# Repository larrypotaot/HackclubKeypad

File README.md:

# 60% Keyboard Addon
* A roughly 3x6 layout for F row and arrow keys, alongside an audio knob. It is hot-swappable for cherry-mx switches.
* Uses QMK software

# PCB

Schematic

Layout: https://www.keyboard-layout-editor.com/#/gists/ed5083c6de0b27ba4e196096e7faea45

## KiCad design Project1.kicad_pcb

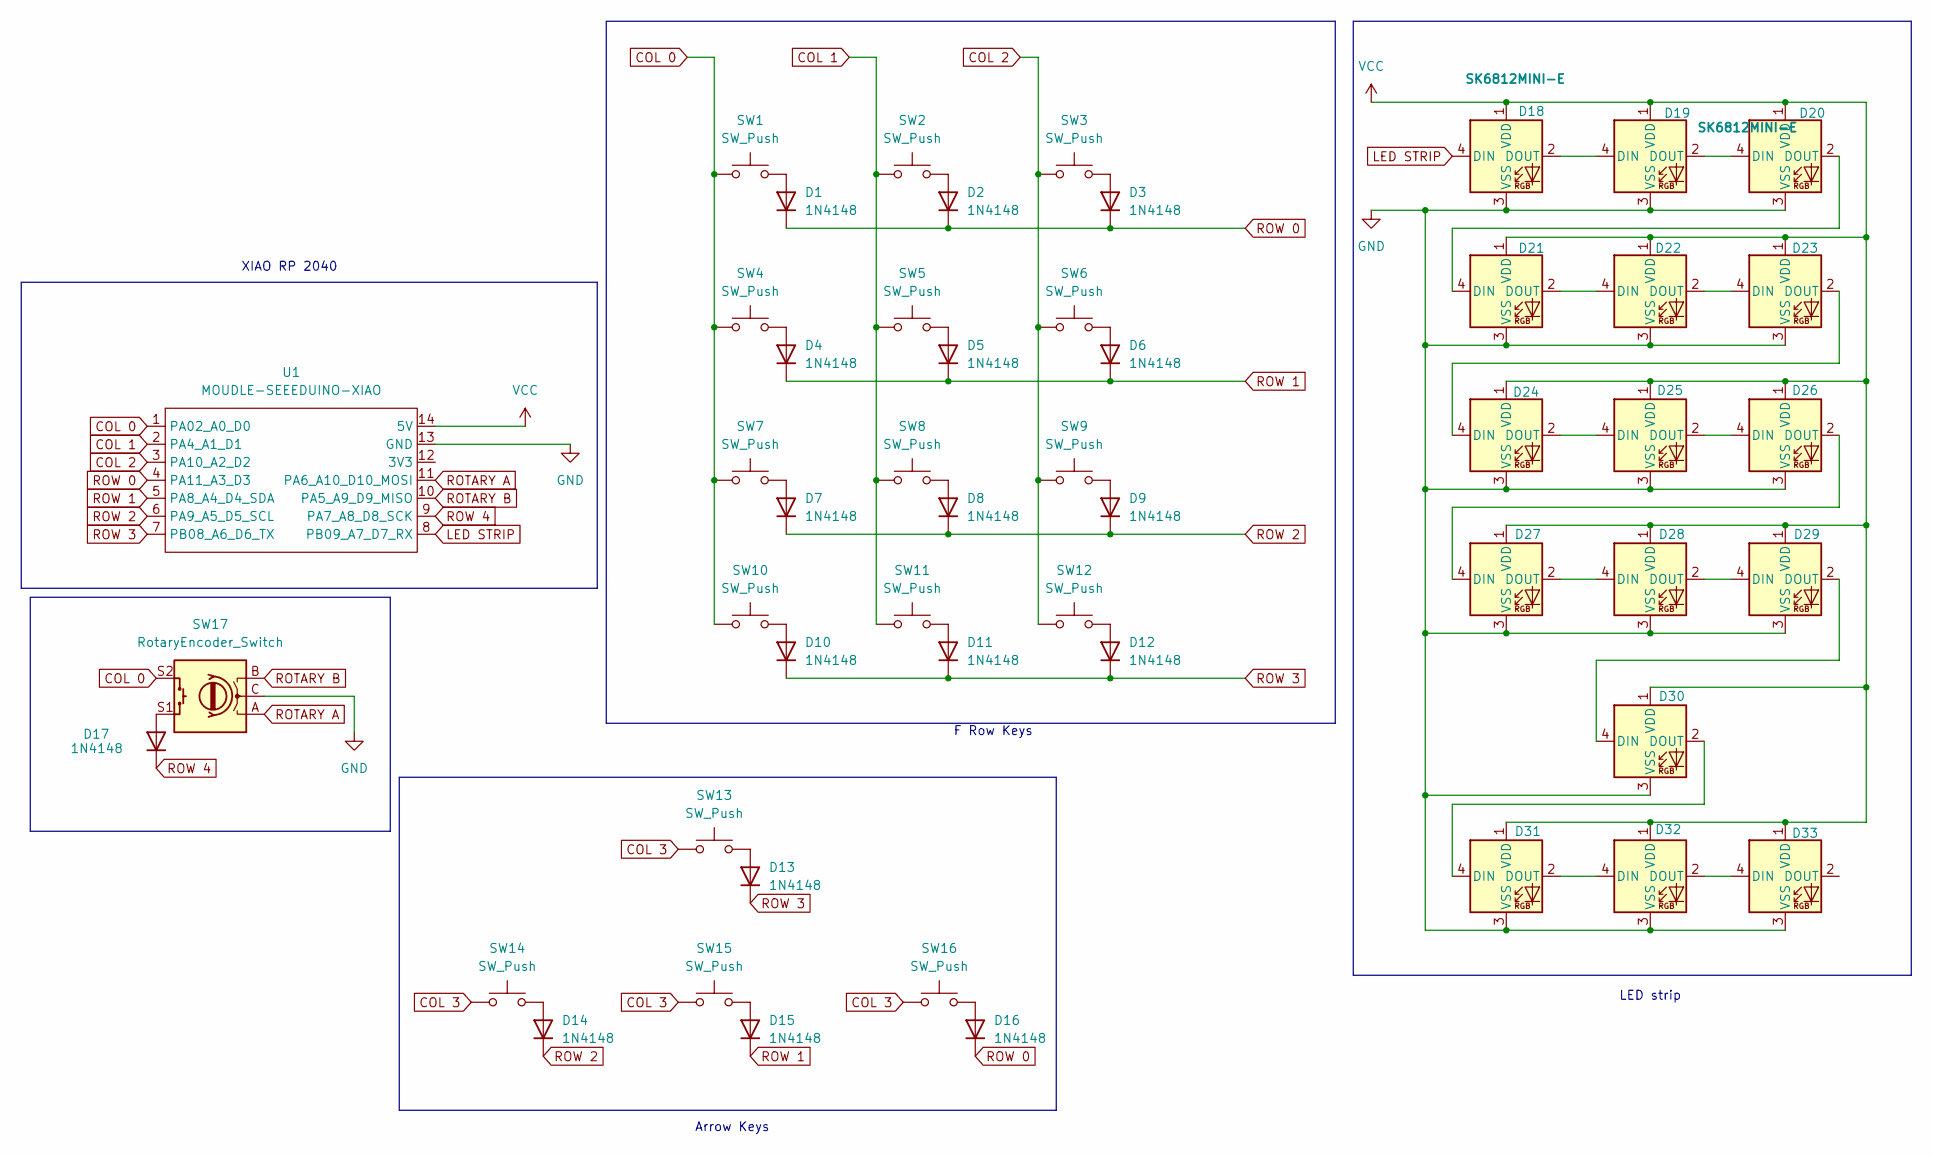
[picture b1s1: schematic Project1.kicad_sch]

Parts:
D1, D2, D3, D4, D5, D6, D7, D8, D9, D10, D11, D12, D13, D14, D15, D16, D17: 1N4148; D_DO-35_SOD27_P7.62mm_Horizontal
D18, D19, D20, D21, D22, D23, D24, D25, D26, D27, D28, D29, D30, D31, D32, D33: SK6812MINI-E; SK6812MINI-E_fixed
SW1, SW2, SW3, SW4, SW5, SW6, SW7, SW8, SW9, SW10, SW11, SW12, SW13, SW14, SW15, SW16: SW_Push; Hotswap_MX_1.00u
SW17: RotaryEncoder_Switch; RotaryEncoder_Alps_EC11E-Switch_Vertical_H20mm
U1: MOUDLE-SEEEDUINO-XIAO; XIAO-Generic-Hybrid-14P-2.54-21X17.8MM

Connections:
COL 0: SW1.1, SW4.1, SW7.1, SW10.1, SW17.S2, U1.1 (PA02_A0_D0)
COL 1: SW2.1, SW5.1, SW8.1, SW11.1, U1.2 (PA4_A1_D1)
COL 2: SW3.1, SW6.1, SW9.1, SW12.1, U1.3 (PA10_A2_D2)
COL 3: SW13.1, SW14.1, SW15.1, SW16.1
GND: D18.3 (VSS), D19.3 (VSS), D20.3 (VSS), D21.3 (VSS), D22.3 (VSS), D23.3 (VSS), D24.3 (VSS), D25.3 (VSS), D26.3 (VSS), D27.3 (VSS), D28.3 (VSS), D29.3 (VSS), D30.3 (VSS), D31.3 (VSS), D32.3 (VSS), D33.3 (VSS), SW17.C, U1.13 (GND)
LED STRIP: D18.4 (DIN), U1.8 (PB09_A7_D7_RX)
unnamed: D1.2 (A), SW1.2
unnamed: D2.2 (A), SW2.2
unnamed: D3.2 (A), SW3.2
unnamed: D4.2 (A), SW4.2
unnamed: D5.2 (A), SW5.2
unnamed: D6.2 (A), SW6.2
unnamed: D7.2 (A), SW7.2
unnamed: D8.2 (A), SW8.2
unnamed: D9.2 (A), SW9.2
unnamed: D10.2 (A), SW10.2
unnamed: D11.2 (A), SW11.2
unnamed: D12.2 (A), SW12.2
unnamed: D13.2 (A), SW13.2
unnamed: D14.2 (A), SW14.2
unnamed: D15.2 (A), SW15.2
unnamed: D16.2 (A), SW16.2
unnamed: D17.2 (A), SW17.S1
unnamed: D18.2 (DOUT), D19.4 (DIN)
unnamed: D19.2 (DOUT), D20.4 (DIN)
unnamed: D20.2 (DOUT), D21.4 (DIN)
unnamed: D21.2 (DOUT), D22.4 (DIN)
unnamed: D22.2 (DOUT), D23.4 (DIN)
unnamed: D23.2 (DOUT), D24.4 (DIN)
unnamed: D24.2 (DOUT), D25.4 (DIN)
unnamed: D25.2 (DOUT), D26.4 (DIN)
unnamed: D26.2 (DOUT), D27.4 (DIN)
unnamed: D27.2 (DOUT), D28.4 (DIN)
unnamed: D28.2 (DOUT), D29.4 (DIN)
unnamed: D29.2 (DOUT), D30.4 (DIN)
unnamed: D30.2 (DOUT), D31.4 (DIN)
unnamed: D31.2 (DOUT), D32.4 (DIN)
unnamed: D32.2 (DOUT), D33.4 (DIN)
ROTARY A: SW17.A, U1.11 (PA6_A10_D10_MOSI)
ROTARY B: SW17.B, U1.10 (PA5_A9_D9_MISO)
ROW 0: D1.1 (K), D2.1 (K), D3.1 (K), D16.1 (K), U1.4 (PA11_A3_D3)
ROW 1: D4.1 (K), D5.1 (K), D6.1 (K), D15.1 (K), U1.5 (PA8_A4_D4_SDA)
ROW 2: D7.1 (K), D8.1 (K), D9.1 (K), D14.1 (K), U1.6 (PA9_A5_D5_SCL)
ROW 3: D10.1 (K), D11.1 (K), D12.1 (K), D13.1 (K), U1.7 (PB08_A6_D6_TX)
ROW 4: D17.1 (K), U1.9 (PA7_A8_D8_SCK)
VCC: D18.1 (VDD), D19.1 (VDD), D20.1 (VDD), D21.1 (VDD), D22.1 (VDD), D23.1 (VDD), D24.1 (VDD), D25.1 (VDD), D26.1 (VDD), D27.1 (VDD), D28.1 (VDD), D29.1 (VDD), D30.1 (VDD), D31.1 (VDD), D32.1 (VDD), D33.1 (VDD), U1.14 (5V)

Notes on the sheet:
Arrow Keys
LED strip
F Row Keys
XIAO RP 2040

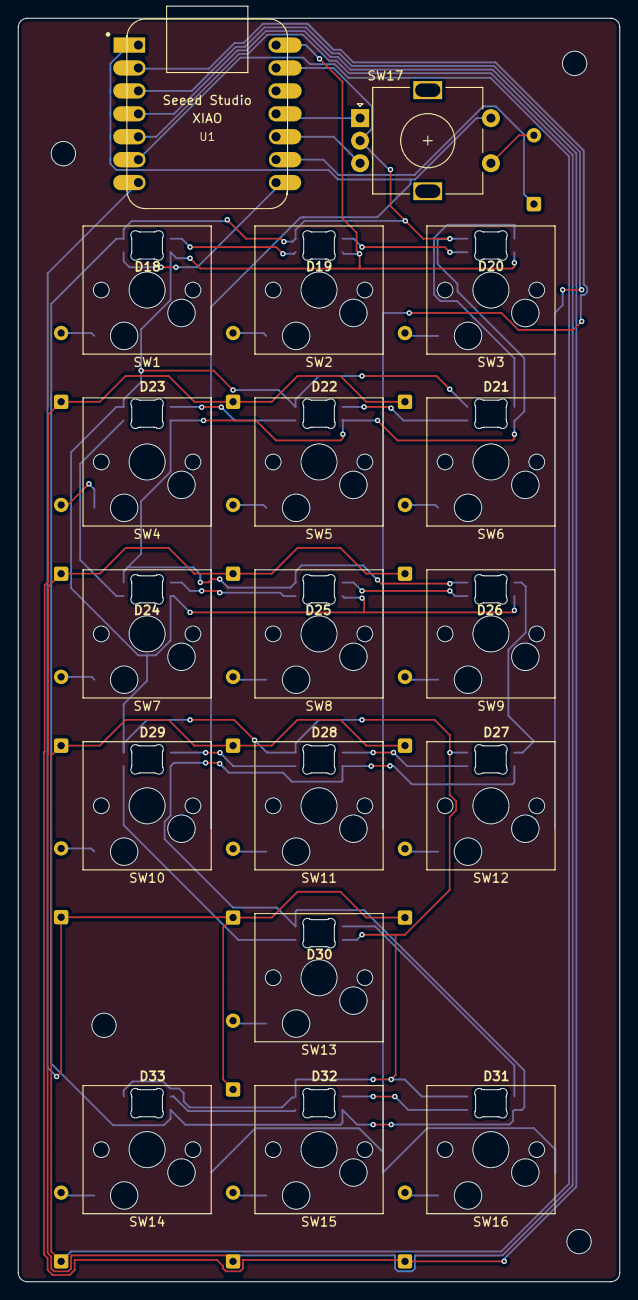
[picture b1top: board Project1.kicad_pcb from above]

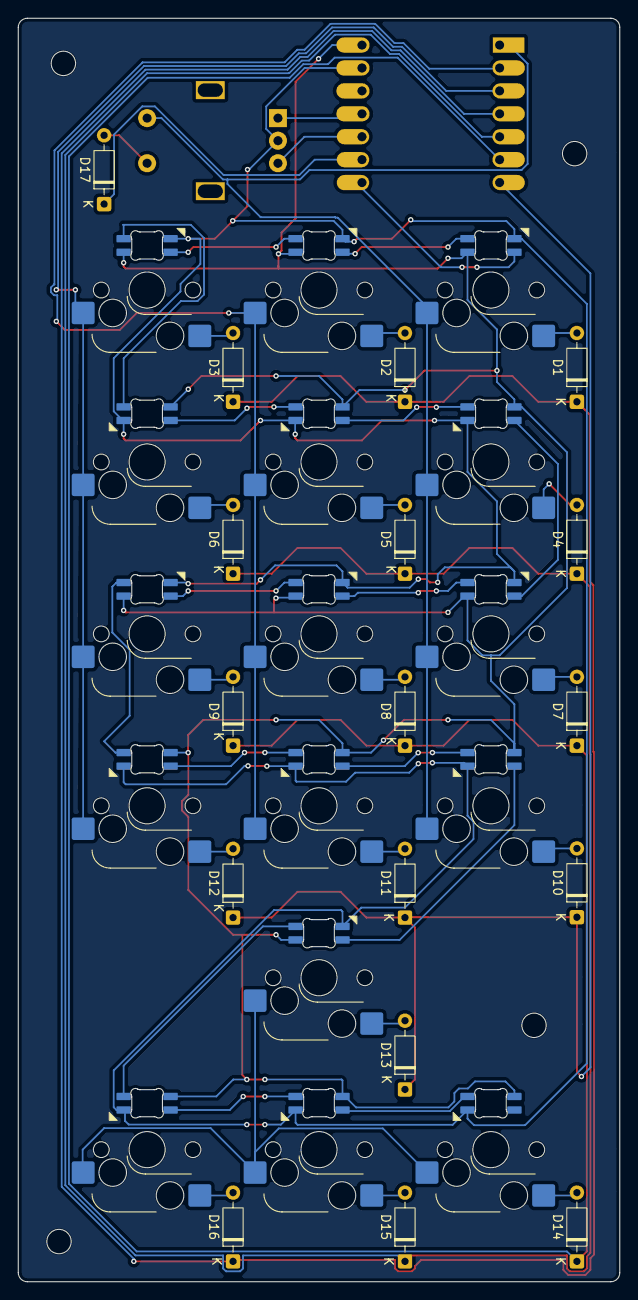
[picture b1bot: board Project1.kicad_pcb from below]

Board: 2 copper layers, 66.6 x 139.9 mm, 51 parts (17 on the bottom side), 46 nets.

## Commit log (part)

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2026-04-01 Create asdf
2026-04-01 Rename Project1.kicad_pcb to KiCad/Project1.kicad_pcb
2026-04-01 Create as
2026-04-01 folders
2026-04-01 Rename Project1.zip to gerber.zip
2026-04-01 Rename Screenshot 2026-03-31 222511.png to images/Screenshot 2026-03-31 222511.png
2026-04-01 Rename Screenshot 2026-03-31 223007.png to images/Screenshot 2026-03-31 223007.png
2026-04-01 Rename Screenshot 2026-03-31 223650.png to images/Screenshot 2026-03-31 223650.png
2026-04-01 Rename Screenshot 2026-03-31 223737.png to images/Screenshot 2026-03-31 223737.png
2026-04-01 Rename Screenshot 2026-03-31 223807.png to images/Screenshot 2026-03-31 223807.png
2026-04-01 Rename Screenshot 2026-03-31 233259.png to PCBorder
2026-05-24 renamed photos
